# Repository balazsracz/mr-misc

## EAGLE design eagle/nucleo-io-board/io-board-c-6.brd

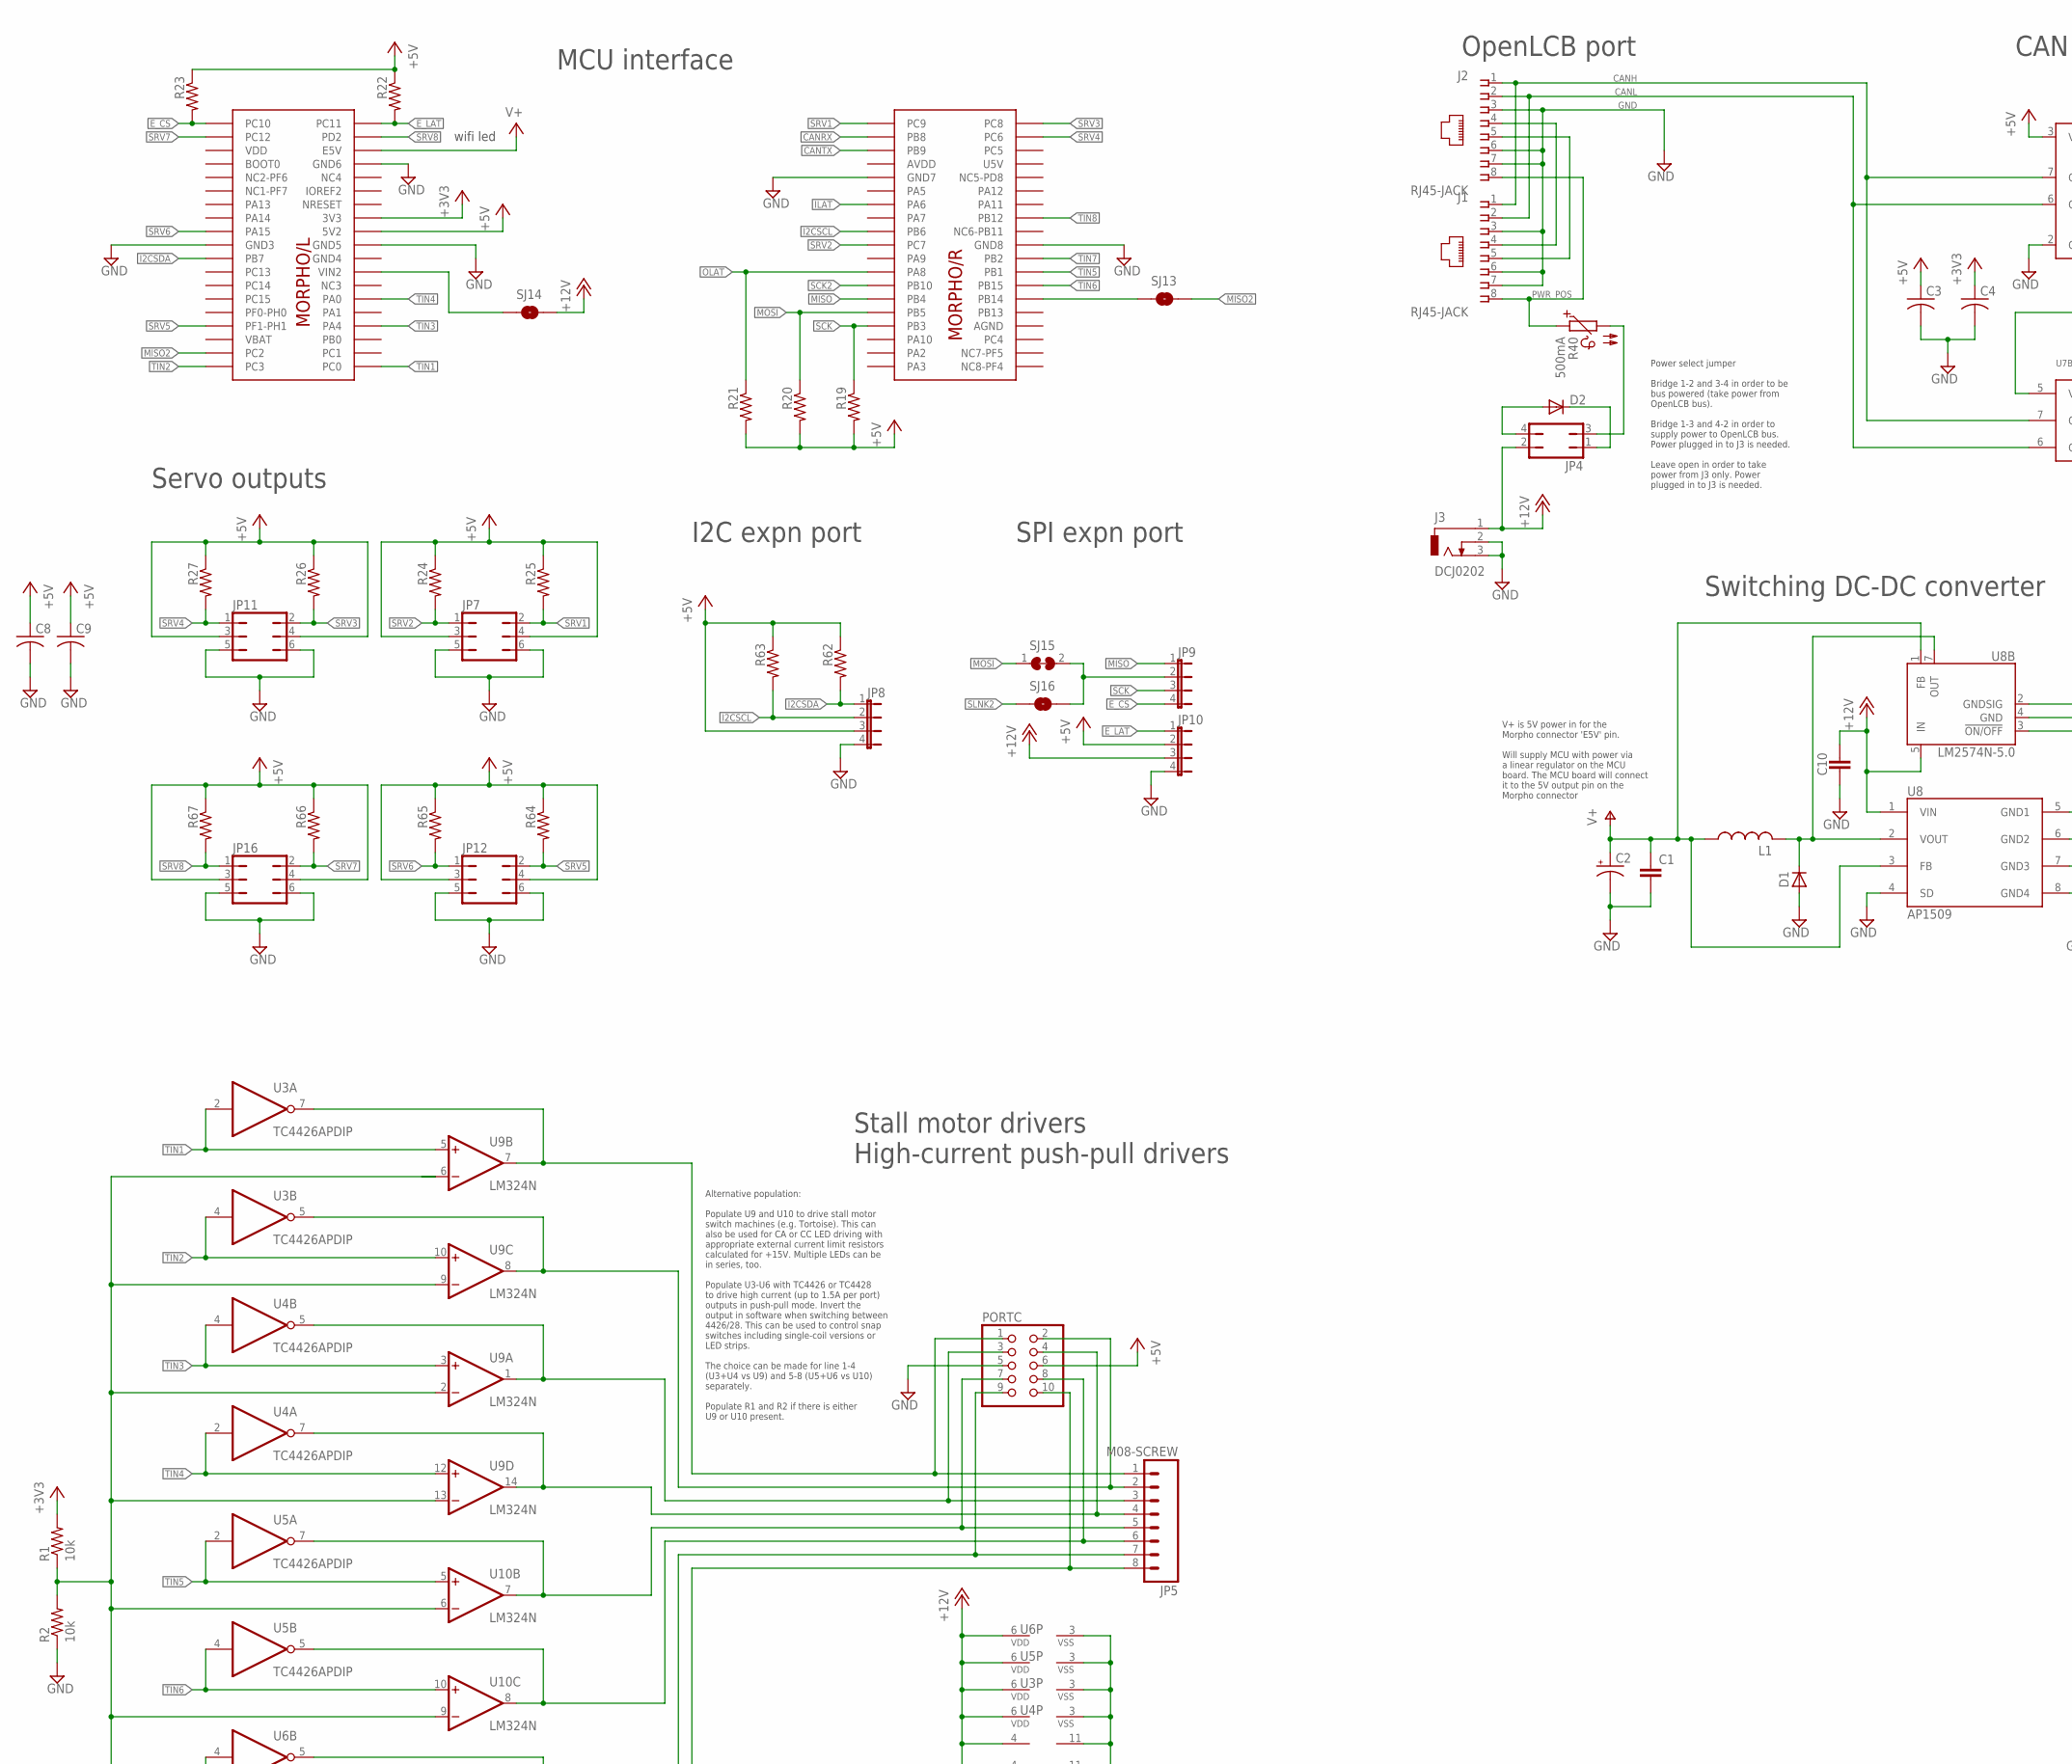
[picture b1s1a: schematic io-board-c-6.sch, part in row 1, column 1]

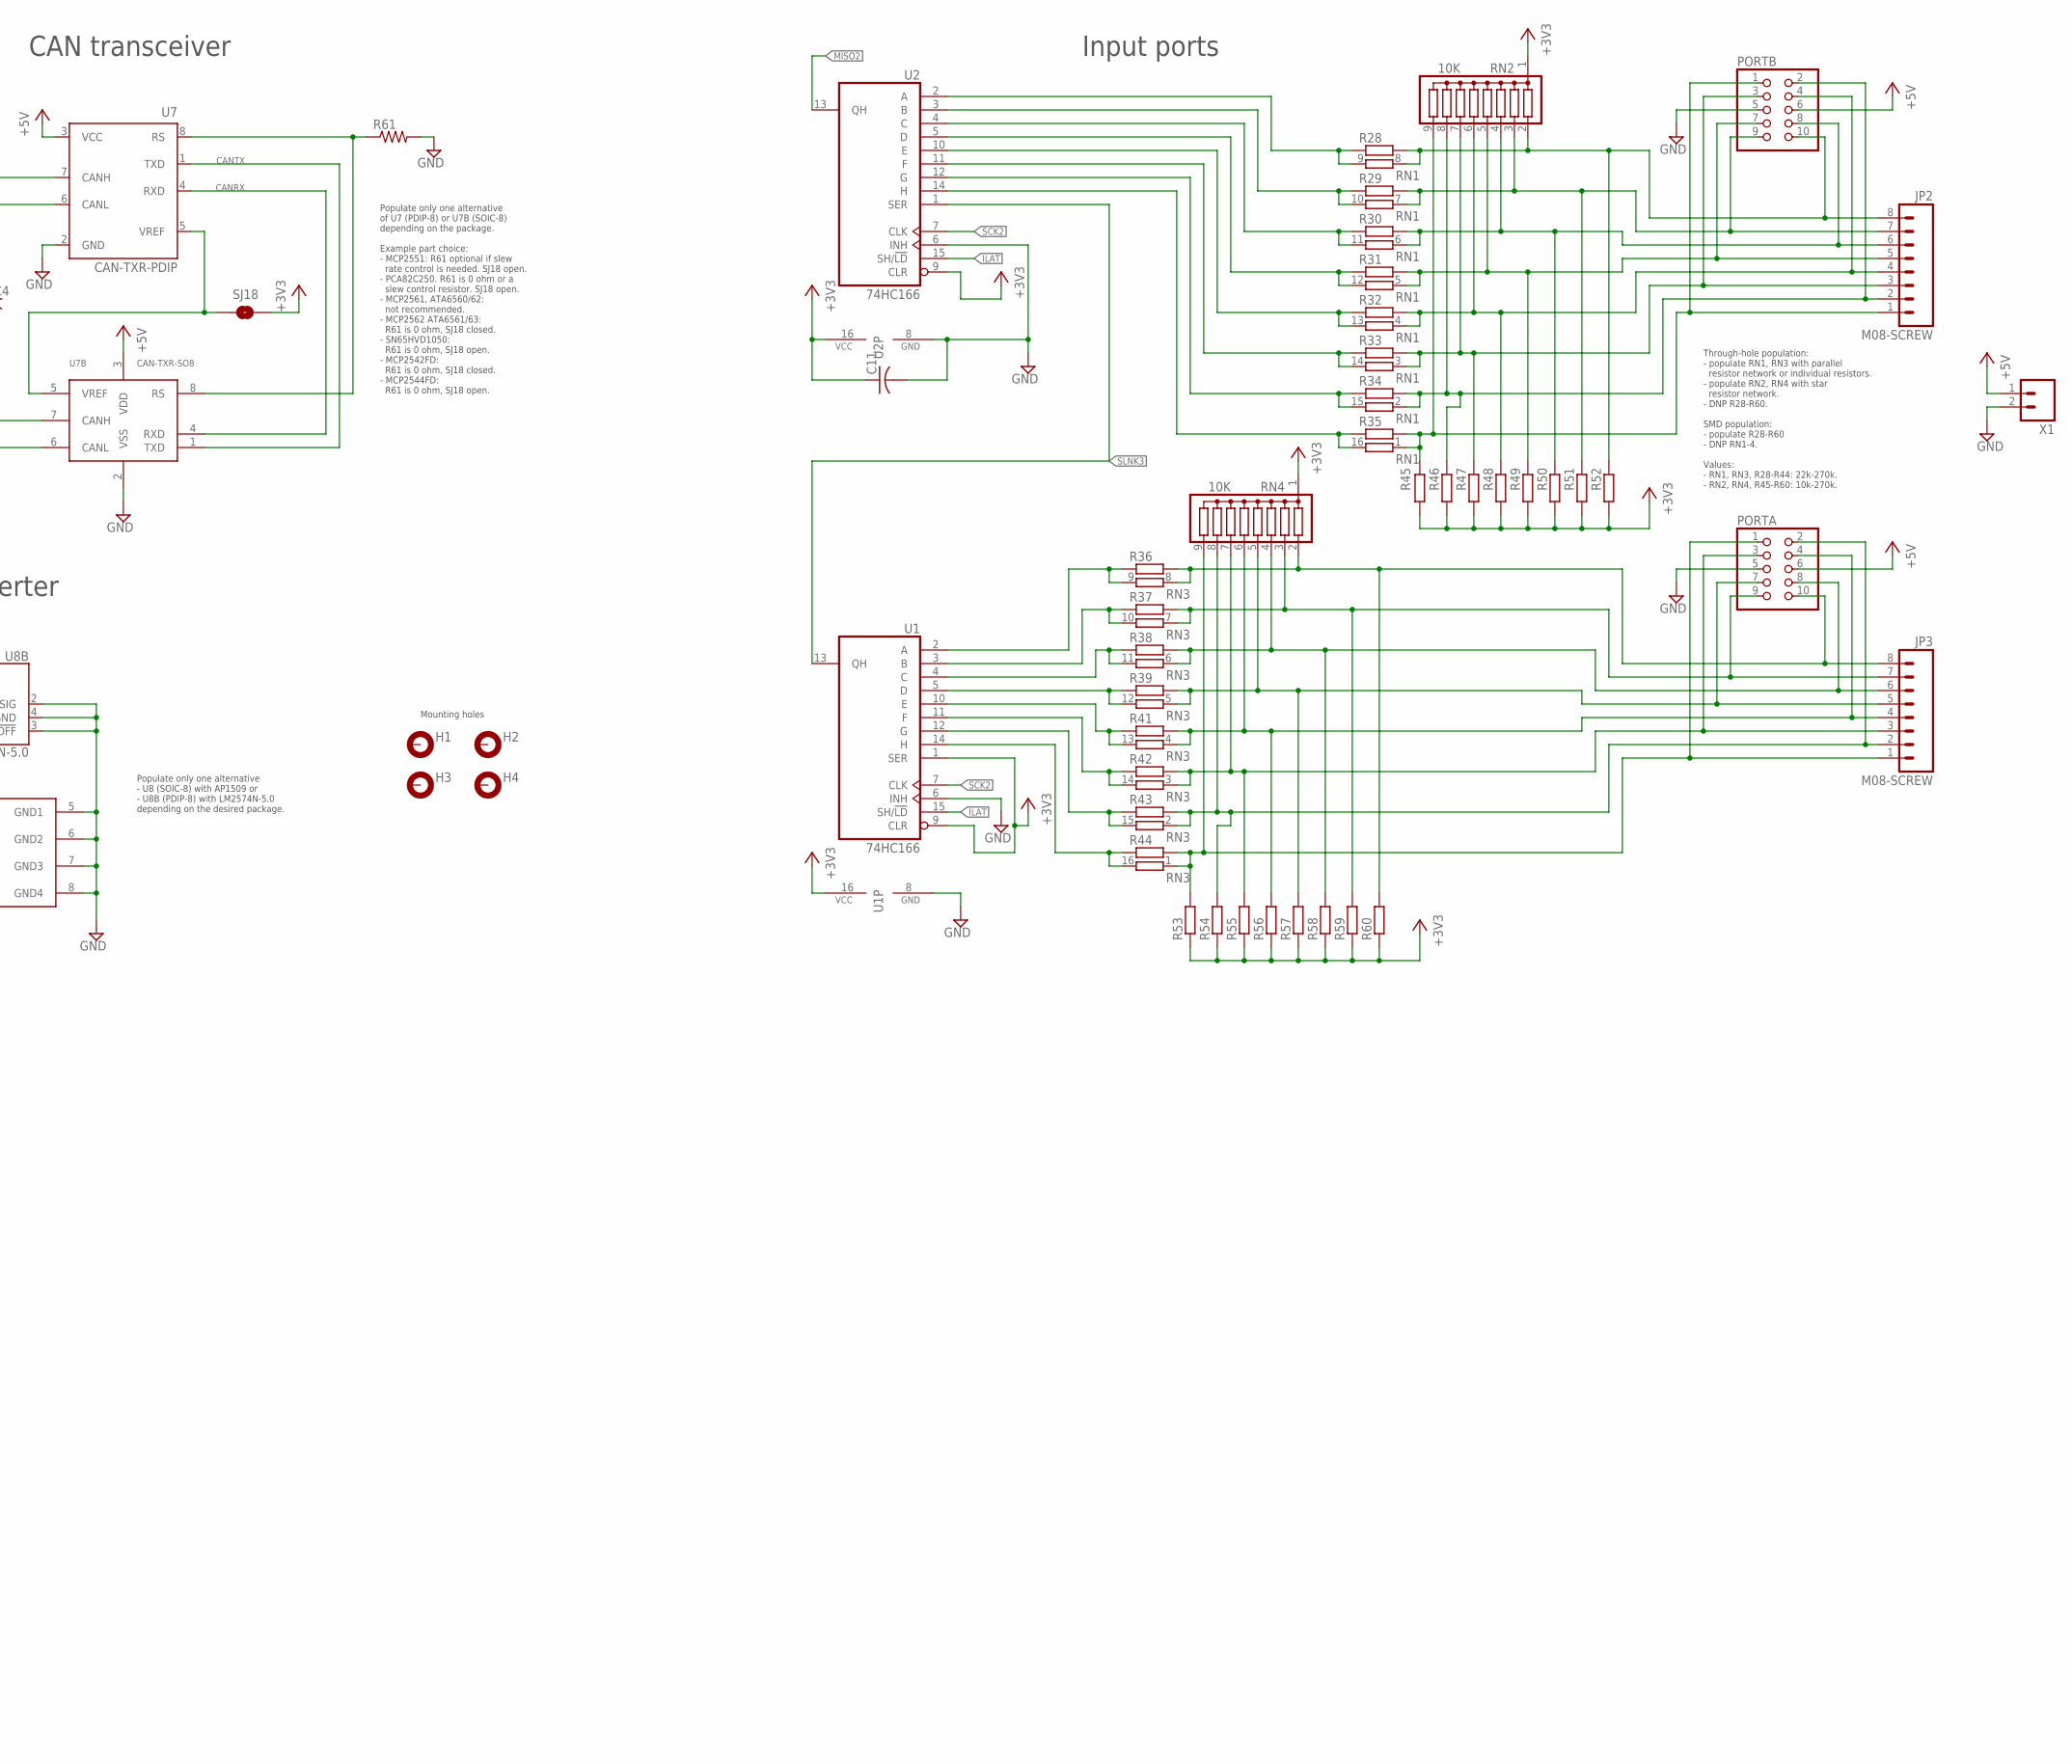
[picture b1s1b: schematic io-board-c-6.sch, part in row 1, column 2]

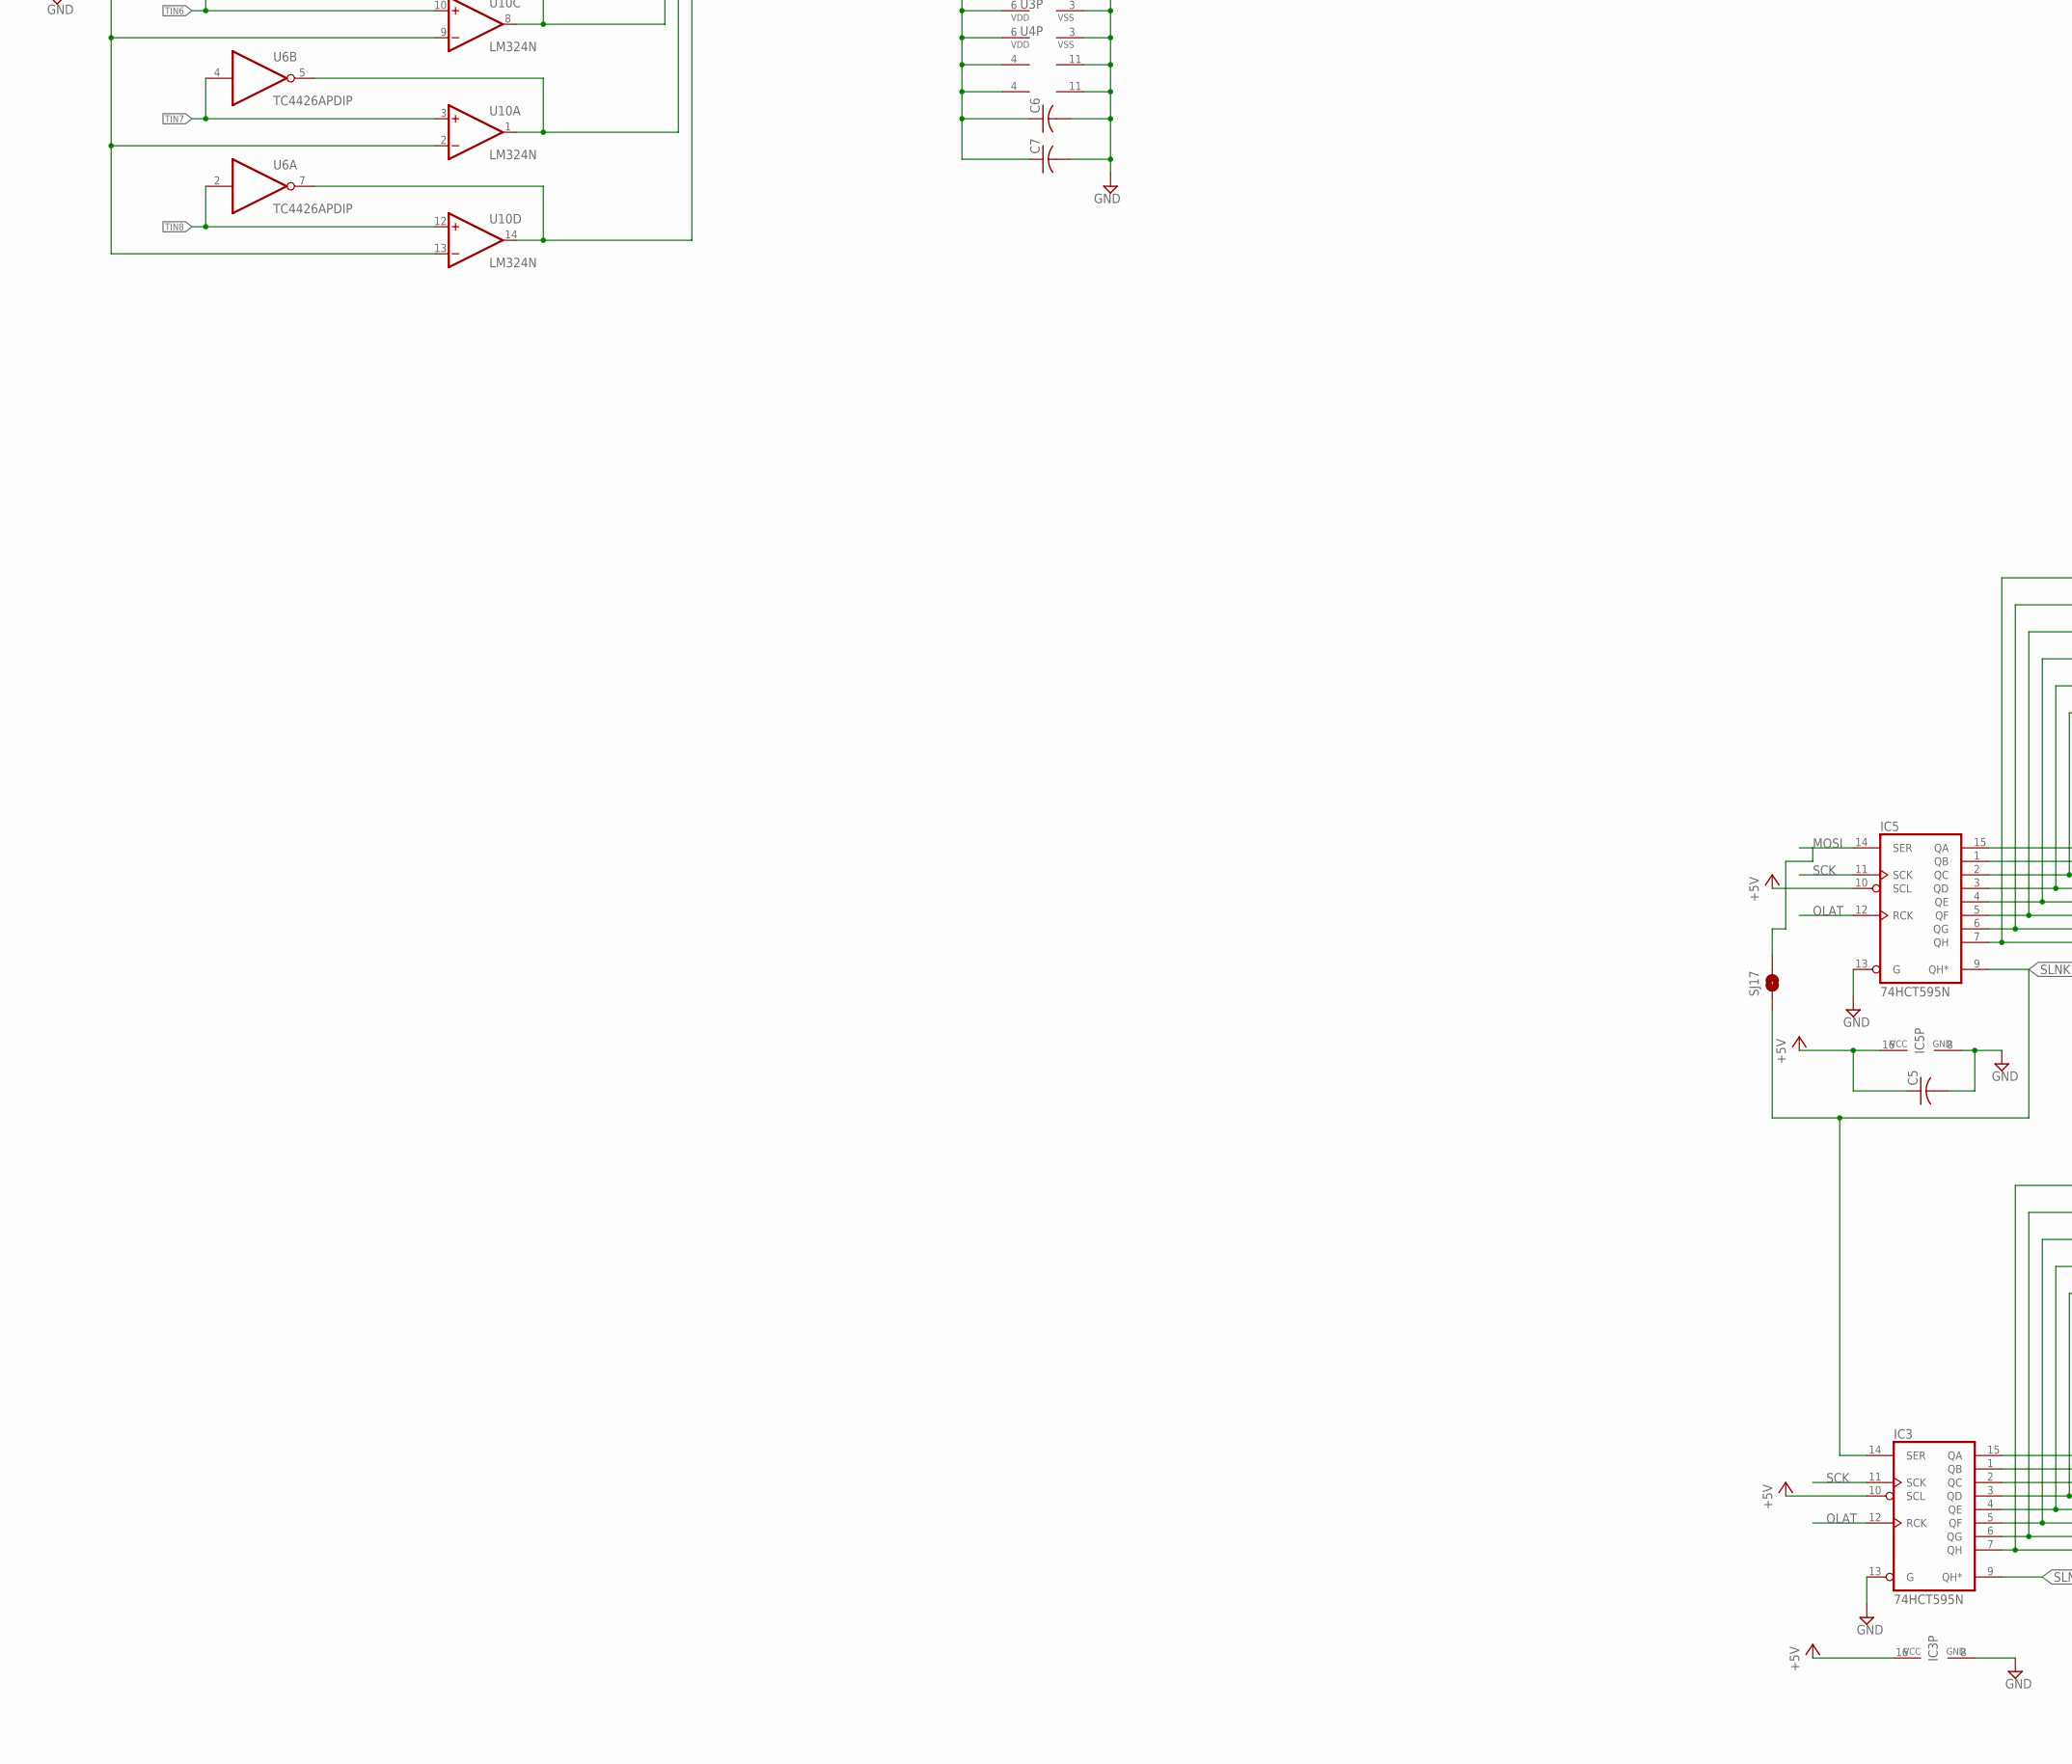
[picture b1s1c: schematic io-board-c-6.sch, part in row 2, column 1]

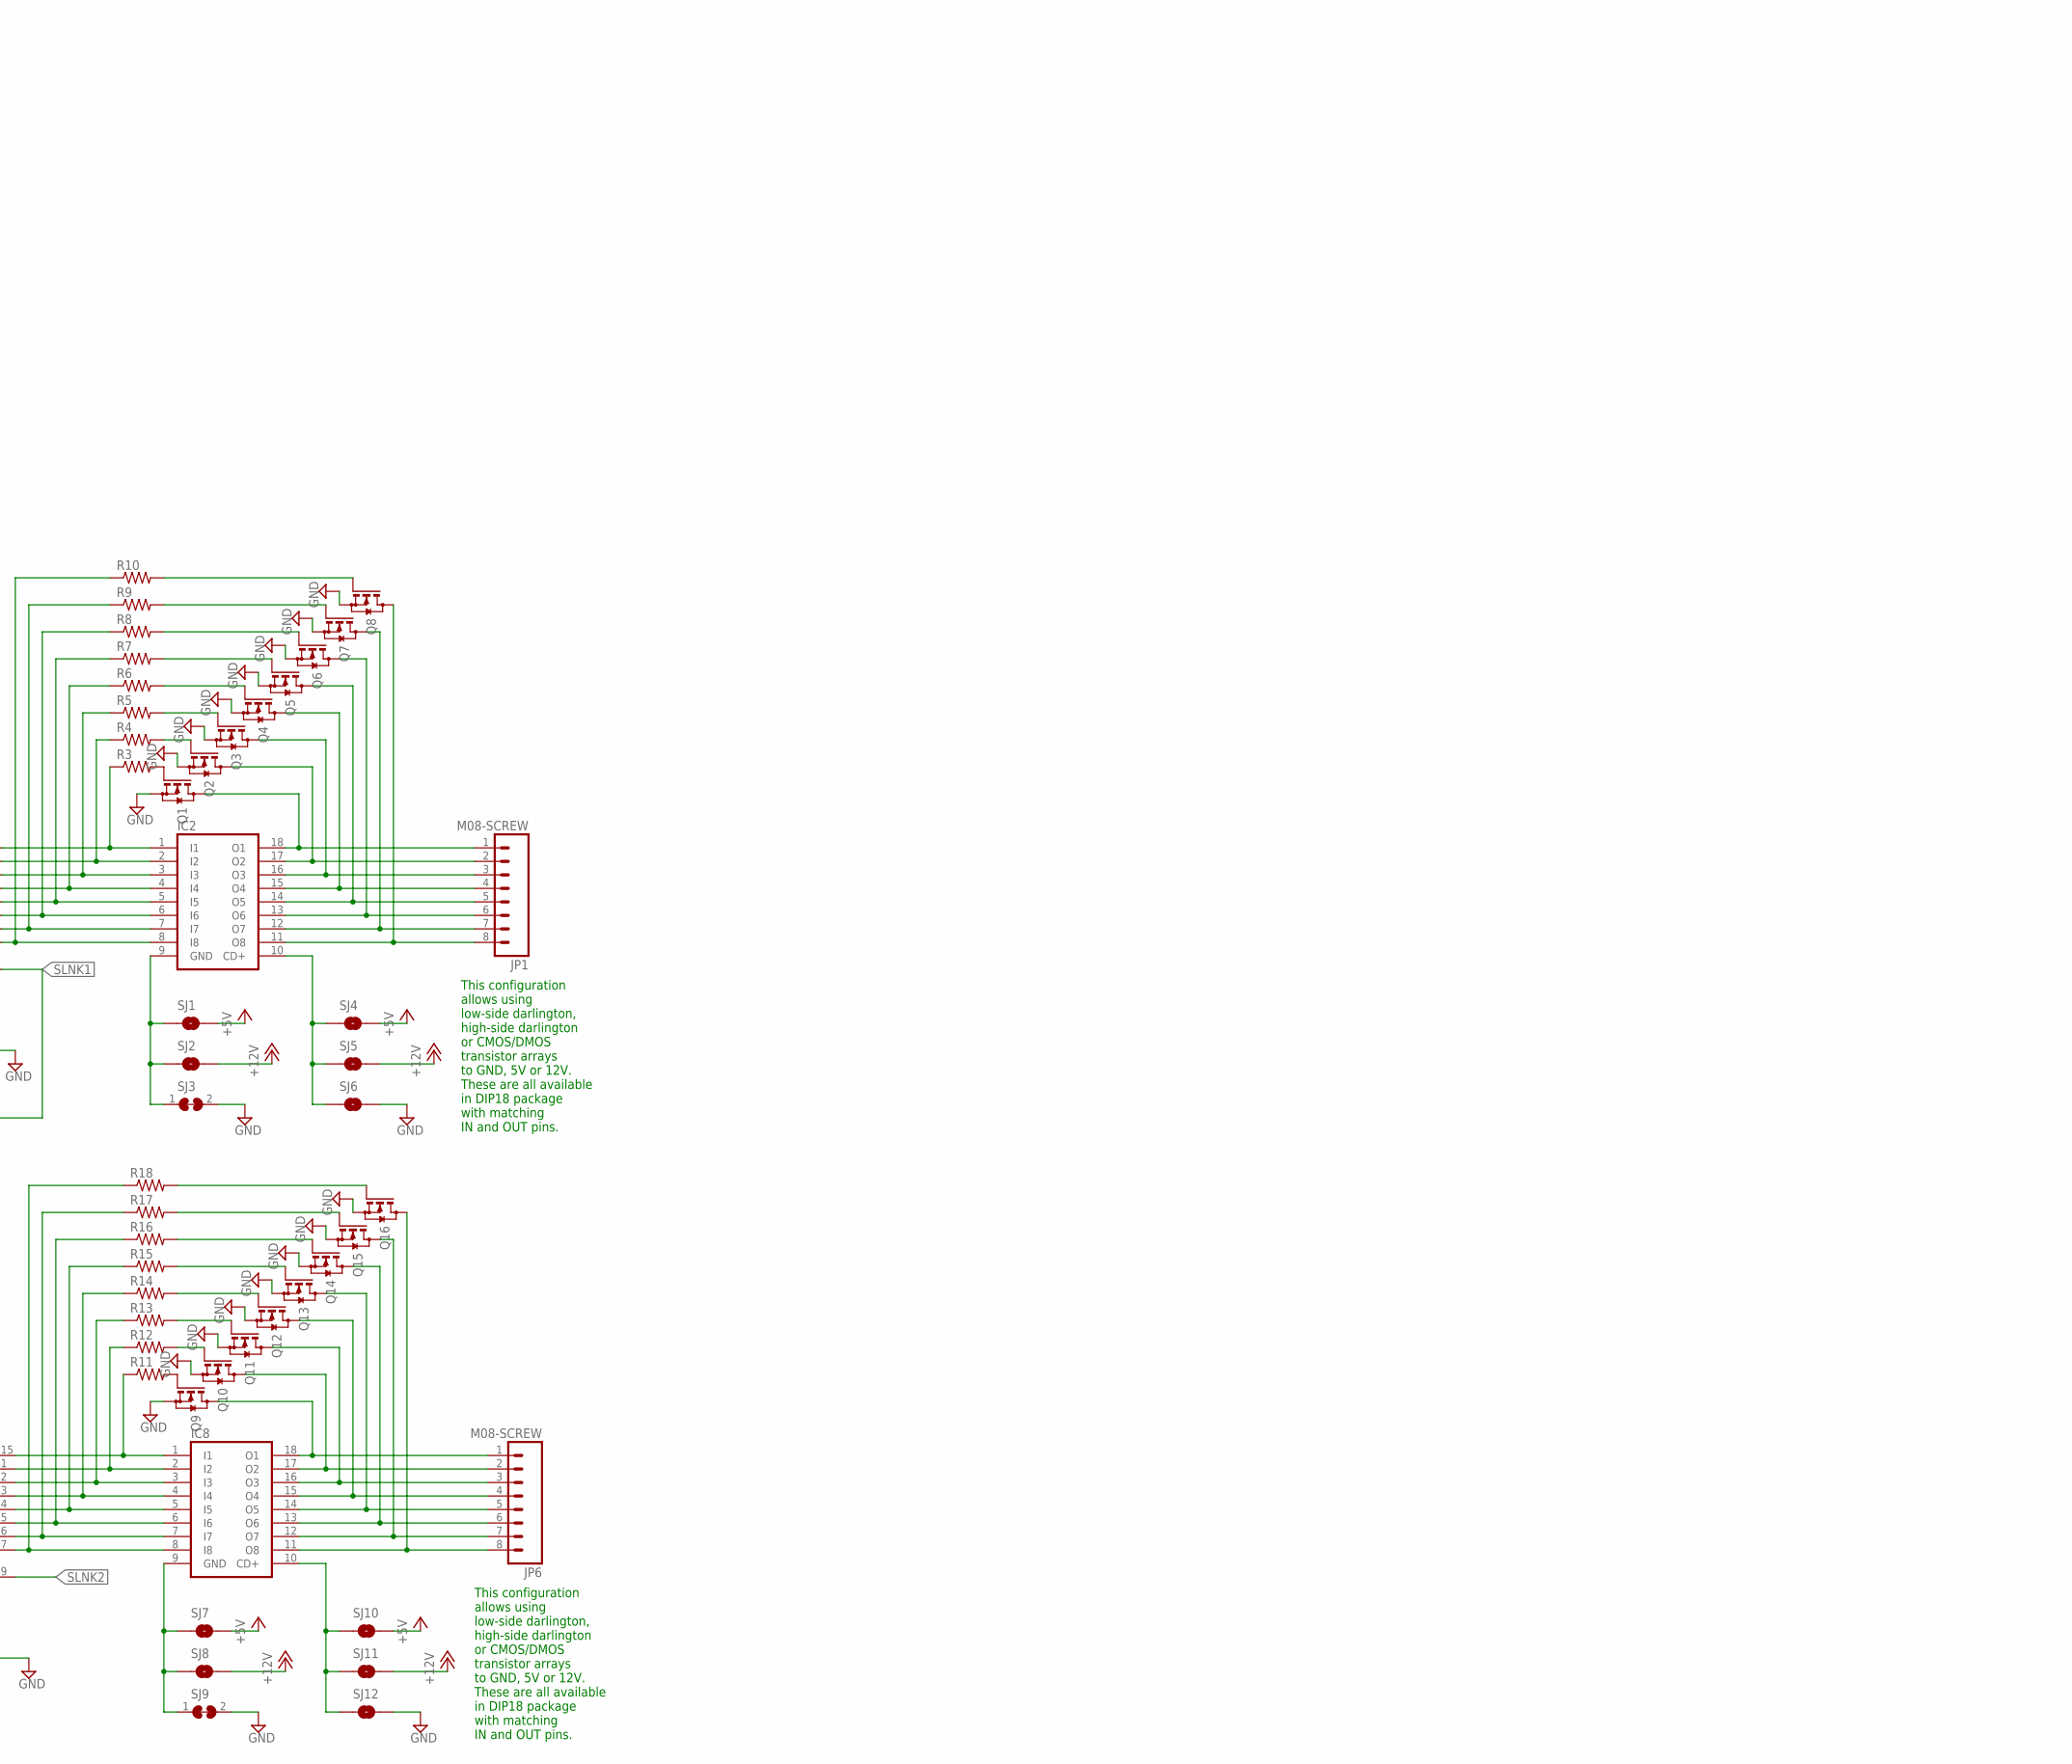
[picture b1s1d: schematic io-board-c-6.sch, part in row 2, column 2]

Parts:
+12V: 9-15V DC; POWER_USAGE
C1, C10: C-EUC1206; C1206
C2: CPOL-USE2.5-5; E2,5-5
C3, C4, C5, C11: C-USC0805; C0805
C6, C7, C8, C9: C-USC1206; C1206
D1, D2: DIODE-DO41-7.6; DO41-7.6
H1, H2, H3, H4: MOUNT-PAD-ROUND3.3; 3,3-PAD
IC2, IC8: ULN2803A; DIL18-THIN
IC3, IC5: 74HCT595N; DIL16
J1, J2: RJ45-JACK; RJ45-PULSE-E5J88
J3: DCJ0202
JP1, JP2, JP3, JP5, JP6: M08-SCREW; 1X08_TERMINAL
JP4: JP2Q
JP7, JP11, JP12, JP16: JP3Q
JP8, JP9, JP10: JP4-FLAT; JP4F
L1: L-US; L5-8,5
PORTA: PINHD-2X5CN; CON10M
PORTB: PINHD-2X5CN; CON10M
PORTC: PINHD-2X5CN; CON10M
Q1, Q2, Q3, Q4, Q5, Q6, Q7, Q8, Q9, Q10, Q11, Q12, Q13, Q14, Q15, Q16: BSS123; SOT23
R1, R2: 10k; R0805
R3, R4, R5, R6, R7, R8, R9, R10, R11, R12, R13, R14, R15, R16, R17, R18: R-US_R0603; R0603
R19, R20, R21, R22, R23, R24, R25, R26, R27, R61, R62, R63, R64, R65, R66, R67: R-US_R0805; R0805
R28, R29, R30, R31, R32, R33, R34, R35, R36, R37, R38, R39, R41, R42, R43, R44, R45, R46, R47, R48, R49, R50, R51, R52, R53, R54, R55, R56, R57, R58, R59, R60: R-EU_R0603; R0603
R40: 500mA; PTC1812
RN1, RN3: 8R-P; DIL16
RN2, RN4: 10K; SIL9
SJ1, SJ2, SJ4, SJ5, SJ6, SJ7, SJ8, SJ10, SJ11, SJ12, SJ13, SJ14, SJ16, SJ17, SJ18: SJRND2; SJ_RND2
SJ3, SJ9, SJ15: SJ-C; SJW-C
U1, U2: 74HC166; DIL16
U3, U4, U5, U6: TC4426APDIP; DIL08-LONG
U7: CAN-TXR-PDIP; DIL08
U7B: CAN-TXR-SO8; SO-08
U8: AP1509; SO-08
U8B: LM2574N-5.0; DIL08
U9, U10: LM324N; DIL14
U$1: NUCLEO_64_GENERIC; NUCLEO_BRD_BASE64
X1: CONNECTOR-M023.5MM-LOCK; SCREWTERMINAL-3.5MM-2_LOCK

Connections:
+3V3: C4.1, C11.1, R1.2, R45.1, R46.2, R47.2, R48.2, R49.2, R50.2, R51.2, R52.2, R53.1, R54.1, R55.1, R56.1, R57.1, R58.1, R59.1, R60.1, RN2.1, RN4.1, SJ18.P$1 (1), U1.1 (SER), U1.9 (CLR), U1.16 (VCC), U2.9 (CLR), U2.16 (VCC), U$1.3V3
+5V: C3.1, C5.1, C8.1, C9.1, IC3.10 (SCL), IC3.16 (VCC), IC5.10 (SCL), IC5.16 (VCC), JP7.3, JP7.4, JP8.3, JP10.2, JP11.3, JP11.4, JP12.3, JP12.4, JP16.3, JP16.4, PORTA.6, PORTB.6, PORTC.6, R19.2, R20.2, R21.2, R22.1, R23.1, R24.1, R25.1, R26.1, R27.1, R62.1, R63.1, R64.1, R65.1, R66.1, R67.1, SJ1.P$2 (2), SJ4.P$2 (2), SJ7.P$2 (2), SJ10.P$2 (2), U7.3 (VCC), U7B.3 (VDD), U$1.5V2, X1.1
+12V: C6.1, C7.1, C10.1, J3.1, JP4.2, JP10.3, SJ2.P$2 (2), SJ5.P$2 (2), SJ8.P$2 (2), SJ11.P$2 (2), SJ14.P$2 (2), U3.6 (VDD), U4.6 (VDD), U5.6 (VDD), U6.6 (VDD), U8.1 (VIN), U8B.5 (IN), U9.4 (V+), U10.4 (V+)
AGND: U$1.AGND
AVDD: U$1.AVDD
CANH: J1.1, J2.1, U7.7 (CANH), U7B.7 (CANH)
CANL: J1.2, J2.2, U7.6 (CANL), U7B.6 (CANL)
CANRX: U7.4 (RXD), U7B.4 (RXD), U$1.PB8
CANTX: U7.1 (TXD), U7B.1 (TXD), U$1.PB9
CAN_RS: R61.1, U7.8 (RS), U7B.8 (RS)
CAN_VIO: SJ18.P$2 (2), U7.5 (VREF), U7B.5 (VREF)
CMPREF: R1.1, R2.2, U9.2 (-IN), U9.6 (-IN), U9.9 (-IN), U9.13 (-IN), U10.2 (-IN), U10.6 (-IN), U10.9 (-IN), U10.13 (-IN)
E_CS: JP9.4, R23.2, U$1.PC10
E_LAT: JP10.1, R22.2, U$1.PC11
E_MOSI: JP9.2, SJ15.2, SJ16.P$2 (2)
GND: C1.2, C2.-, C3.2, C4.2, C5.2, C6.2, C7.2, C8.2, C9.2, C10.2, C11.2, D1.A, IC3.8 (GND), IC3.13 (G), IC5.8 (GND), IC5.13 (G), J1.3, J1.6, J1.7, J2.3, J2.6, J2.7, J3.2, J3.3, JP7.5, JP7.6, JP8.4, JP10.4, JP11.5, JP11.6, JP12.5, JP12.6, JP16.5, JP16.6, PORTA.5, PORTB.5, PORTC.5, Q1.2 (S), Q2.2 (S), Q3.2 (S), Q4.2 (S), Q5.2 (S), Q6.2 (S), Q7.2 (S), Q8.2 (S), Q9.2 (S), Q10.2 (S), Q11.2 (S), Q12.2 (S), Q13.2 (S), Q14.2 (S), Q15.2 (S), Q16.2 (S), R2.1, R61.2, SJ3.2, SJ6.P$2 (2), SJ9.2, SJ12.P$2 (2), U1.6 (INH), U1.8 (GND), U2.6 (INH), U2.8 (GND), U3.3 (VSS), U4.3 (VSS), U5.3 (VSS), U6.3 (VSS), U7.2 (GND), U7B.2 (VSS), U8.4 (SD), U8.5 (GND1), U8.6 (GND2), U8.7 (GND3), U8.8 (GND4), U8B.2 (GNDSIG), U8B.3 (!ON/OFF), U8B.4 (GND), U9.11 (V-), U10.11 (V-), U$1.GND3, U$1.GND5, U$1.GND6, U$1.GND7, U$1.GND8, X1.2
GND4: U$1.GND4
I2CSCL: JP8.2, R63.2, U$1.PB6
I2CSDA: JP8.1, R62.2, U$1.PB7
ILAT: U1.15 (SH/!LD), U2.15 (SH/!LD), U$1.PA6
LPOWA: IC8.9 (GND), SJ7.P$1 (1), SJ8.P$1 (1), SJ9.1
LPOWB: IC8.10 (CD+), SJ10.P$1 (1), SJ11.P$1 (1), SJ12.P$1 (1)
MISO: JP9.1, U$1.PB4
MISO2: SJ13.P$2 (2), U2.13 (QH), U$1.PC2
MISO2_ALT: SJ13.P$1 (1), U$1.PB14
MOSI: IC5.14 (SER), R20.1, SJ15.1, SJ17.P$2 (2), U$1.PB5
unnamed: IC2.1 (I1), IC5.15 (QA), R3.1
unnamed: IC2.18 (O1), JP1.1, Q1.3 (D)
unnamed: IC2.2 (I2), IC5.1 (QB), R4.1
unnamed: J1.4, J2.4
unnamed: J1.5, J2.5
unnamed: JP3.8, PORTA.10, R36.2, R60.2, RN3.8 (1), RN4.2
unnamed: IC2.17 (O2), JP1.2, Q2.3 (D)
unnamed: IC2.3 (I3), IC5.2 (QC), R5.1
unnamed: IC2.16 (O3), JP1.3, Q3.3 (D)
unnamed: IC2.4 (I4), IC5.3 (QD), R6.1
unnamed: IC2.15 (O4), JP1.4, Q4.3 (D)
unnamed: IC2.5 (I5), IC5.4 (QE), R7.1
unnamed: IC2.14 (O5), JP1.5, Q5.3 (D)
unnamed: JP3.7, PORTA.9, R37.2, R59.2, RN3.7 (1), RN4.3
unnamed: JP3.6, PORTA.8, R38.2, R58.2, RN3.6 (1), RN4.4
unnamed: Q4.1 (G), R6.2
unnamed: IC2.6 (I6), IC5.5 (QF), R8.1
unnamed: IC2.13 (O6), JP1.6, Q6.3 (D)
unnamed: JP3.4, PORTA.4, R41.2, R56.2, RN3.4 (1), RN4.6
unnamed: JP3.3, PORTA.3, R42.2, R55.2, RN3.3 (1), RN4.7
unnamed: JP2.6, PORTB.8, R30.2, R50.1, RN1.6 (1), RN2.4
unnamed: JP3.1, PORTA.1, R44.2, R53.2, RN3.1, RN4.9
unnamed: R36.1, RN3.9 (2), U1.2 (A)
unnamed: R37.1, RN3.10 (2), U1.3 (B)
unnamed: JP2.8, PORTB.10, R28.2, R52.1, RN1.8 (1), RN2.2
unnamed: JP2.7, PORTB.9, R29.2, R51.1, RN1.7 (1), RN2.3
unnamed: Q5.1 (G), R7.2
unnamed: JP2.5, PORTB.7, R31.2, R49.1, RN1.5 (1), RN2.5
unnamed: R38.1, RN3.11 (2), U1.4 (C)
unnamed: R39.1, RN3.12 (2), U1.5 (D)
unnamed: R41.1, RN3.13 (2), U1.10 (E)
unnamed: R42.1, RN3.14 (2), U1.11 (F)
unnamed: JP2.4, PORTB.4, R32.2, R48.1, RN1.4 (1), RN2.6
unnamed: JP2.3, PORTB.3, R33.2, R47.1, RN1.3 (1), RN2.7
unnamed: JP2.2, PORTB.2, R34.2, R46.1, RN1.2 (1), RN2.8
unnamed: JP2.1, PORTB.1, R35.2, R45.2, RN1.1, RN2.9
unnamed: R43.1, RN3.15 (2), U1.12 (G)
unnamed: R44.1, RN3.16 (2), U1.14 (H)
unnamed: IC2.7 (I7), IC5.6 (QG), R9.1
unnamed: IC2.12 (O7), JP1.7, Q7.3 (D)
unnamed: IC2.8 (I8), IC5.7 (QH), R10.1
unnamed: IC2.11 (O8), JP1.8, Q8.3 (D)
unnamed: Q6.1 (G), R8.2
unnamed: R28.1, RN1.9 (2), U2.2 (A)
unnamed: D2.C, JP4.1
unnamed: D2.A, JP4.4
unnamed: R29.1, RN1.10 (2), U2.3 (B)
unnamed: R30.1, RN1.11 (2), U2.4 (C)
unnamed: R31.1, RN1.12 (2), U2.5 (D)
unnamed: R32.1, RN1.13 (2), U2.10 (E)
unnamed: R33.1, RN1.14 (2), U2.11 (F)
unnamed: R34.1, RN1.15 (2), U2.12 (G)
unnamed: R35.1, RN1.16 (2), U2.14 (H)
unnamed: IC3.15 (QA), IC8.1 (I1), R11.1
unnamed: JP4.3, R40.2
unnamed: SJ14.P$1 (1), U$1.VIN2
unnamed: Q7.1 (G), R9.2
unnamed: IC8.11 (O8), JP6.8, Q16.3 (D)
unnamed: Q1.1 (G), R3.2
unnamed: Q2.1 (G), R4.2
unnamed: JP3.5, PORTA.7, R39.2, R57.2, RN3.5 (1), RN4.5
unnamed: JP3.2, PORTA.2, R43.2, R54.2, RN3.2 (1), RN4.8
unnamed: Q8.1 (G), R10.2
unnamed: IC8.18 (O1), JP6.1, Q9.3 (D)
unnamed: Q3.1 (G), R5.2
unnamed: IC3.1 (QB), IC8.2 (I2), R12.1
unnamed: IC8.17 (O2), JP6.2, Q10.3 (D)
unnamed: IC3.2 (QC), IC8.3 (I3), R13.1
unnamed: IC8.16 (O3), JP6.3, Q11.3 (D)
unnamed: IC3.3 (QD), IC8.4 (I4), R14.1
unnamed: IC8.15 (O4), JP6.4, Q12.3 (D)
unnamed: IC3.4 (QE), IC8.5 (I5), R15.1
unnamed: IC8.14 (O5), JP6.5, Q13.3 (D)
unnamed: IC3.5 (QF), IC8.6 (I6), R16.1
unnamed: IC8.13 (O6), JP6.6, Q14.3 (D)
unnamed: IC3.6 (QG), IC8.7 (I7), R17.1
unnamed: IC8.12 (O7), JP6.7, Q15.3 (D)
unnamed: IC3.7 (QH), IC8.8 (I8), R18.1
unnamed: Q9.1 (G), R11.2
unnamed: Q10.1 (G), R12.2
unnamed: Q11.1 (G), R13.2
unnamed: Q12.1 (G), R14.2
unnamed: Q13.1 (G), R15.2
unnamed: Q14.1 (G), R16.2
unnamed: Q15.1 (G), R17.2
unnamed: Q16.1 (G), R18.2
OLAT: IC3.12 (RCK), IC5.12 (RCK), R21.1, U$1.PA8
PWR_POS: J1.8, J2.8, R40.1
RPOWA: IC2.9 (GND), SJ1.P$1 (1), SJ2.P$1 (1), SJ3.1
RPOWB: IC2.10 (CD+), SJ4.P$1 (1), SJ5.P$1 (1), SJ6.P$1 (1)
SCK: IC3.11 (SCK), IC5.11 (SCK), JP9.3, R19.1, U$1.PB3
SCK2: U1.7 (CLK), U2.7 (CLK), U$1.PB10
SLNK1: IC3.14 (SER), IC5.9 (QH*), SJ17.P$1 (1)
SLNK2: IC3.9 (QH*), SJ16.P$1 (1)
SLNK3: U1.13 (QH), U2.1 (SER)
SRV1: JP7.2, R25.2, U$1.PC9
SRV2: JP7.1, R24.2, U$1.PC7
SRV3: JP11.2, R26.2, U$1.PC8
SRV4: JP11.1, R27.2, U$1.PC6
SRV5: JP12.2, R64.2, U$1.PF1-PH1
SRV6: JP12.1, R65.2, U$1.PA15
SRV7: JP16.2, R66.2, U$1.PC12
SRV8: JP16.1, R67.2, U$1.PD2
SW: D1.C, L1.2, U8.2 (VOUT), U8B.7 (OUT)
TIN1: U3.2 (I), U9.5 (+IN), U$1.PC0
TIN2: U3.4 (I), U9.10 (+IN), U$1.PC3
TIN3: U4.4 (I), U9.3 (+IN), U$1.PA4
TIN4: U4.2 (I), U9.12 (+IN), U$1.PA0
TIN5: U5.2 (I), U10.5 (+IN), U$1.PB1
TIN6: U5.4 (I), U10.10 (+IN), U$1.PB15
TIN7: U6.4 (I), U10.3 (+IN), U$1.PB2
TIN8: U6.2 (I), U10.12 (+IN), U$1.PB12
TOUT1: JP5.1, PORTC.1, U3.7 (O), U9.7 (OUT)
TOUT2: JP5.2, PORTC.2, U3.5 (O), U9.8 (OUT)
TOUT3: JP5.3, PORTC.3, U4.5 (O), U9.1 (OUT)
TOUT4: JP5.4, PORTC.4, U4.7 (O), U9.14 (OUT)
TOUT5: JP5.5, PORTC.7, U5.7 (O), U10.7 (OUT)
TOUT6: JP5.6, PORTC.8, U5.5 (O), U10.8 (OUT)
TOUT7: JP5.7, PORTC.9, U6.5 (O), U10.1 (OUT)
TOUT8: JP5.8, PORTC.10, U6.7 (O), U10.14 (OUT)
U5V: U$1.U5V
V+: C1.1, C2.+, L1.1, U8.3 (FB), U8B.1 (FB), U$1.E5V
VBAT: U$1.VBAT
VDD: U$1.VDD

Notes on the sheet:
This configuration allows using low-side darlington, high-side darlington or CMOS/DMOS transistor arrays to GND, 5V or 12V. These are all available in DIP18 package with matching IN and OUT pins.
wifi led
Servo outputs
I2C expn port
SPI expn port
MCU interface
Populate only one alternative of U7 (PDIP-8) or U7B (SOIC-8) depending on the package. Example part choice: - MCP2551: R61 optional if slew rate control is needed. SJ18 open. - PCA82C250. R61 is 0 ohm or a slew control resistor. SJ18 open. - MCP2561, ATA6560/62: not recommended. - MCP2562 ATA6561/6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
OpenLCB port
CAN transceiver
Power select jumper Bridge 1-2 and 3-4 in order to be bus powered (take power from OpenLCB bus). Bridge 1-3 and 4-2 in order to supply power to OpenLCB bus. Power plugged in to J3 is needed. Leave open in order to take power from J3 only. Power plugged in to J3 is needed.
Switching DC-DC converter
Populate only one alternative - U8 (SOIC-8) with AP1509 or - U8B (PDIP-8) with LM2574N-5.0 depending on the desired package.
V+ is 5V power in for the Morpho connector 'E5V' pin. Will supply MCU with power via a linear regulator on the MCU board. The MCU board will connect it to the 5V output pin on the Morpho connector
Mounting holes
Input ports
Through-hole population: - populate RN1, RN3 with parallel resistor network or individual resistors. - populate RN2, RN4 with star resistor network. - DNP R28-R60. SMD population: - populate R28-R60 - DNP RN1-4. Values: - RN1, RN3, R28-R44: 22k-270k. - RN2, RN4, R45-R60: 10k-270k.
Stall motor drivers High-current push-pull drivers
Alternative population: Populate U9 and U10 to drive stall motor switch machines (e.g. Tortoise). This can also be used for CA or CC LED driving with appropriate external current limit resistors calculated for +15V. Multiple LEDs can be in series, too. Populate U3-U6 with TC4426 or TC4428 to drive 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

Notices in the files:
eagle/nucleo-io-board/io-board-c-6.sch:
LICENSE: [placeholder for license]
LICENSE: foo bar
